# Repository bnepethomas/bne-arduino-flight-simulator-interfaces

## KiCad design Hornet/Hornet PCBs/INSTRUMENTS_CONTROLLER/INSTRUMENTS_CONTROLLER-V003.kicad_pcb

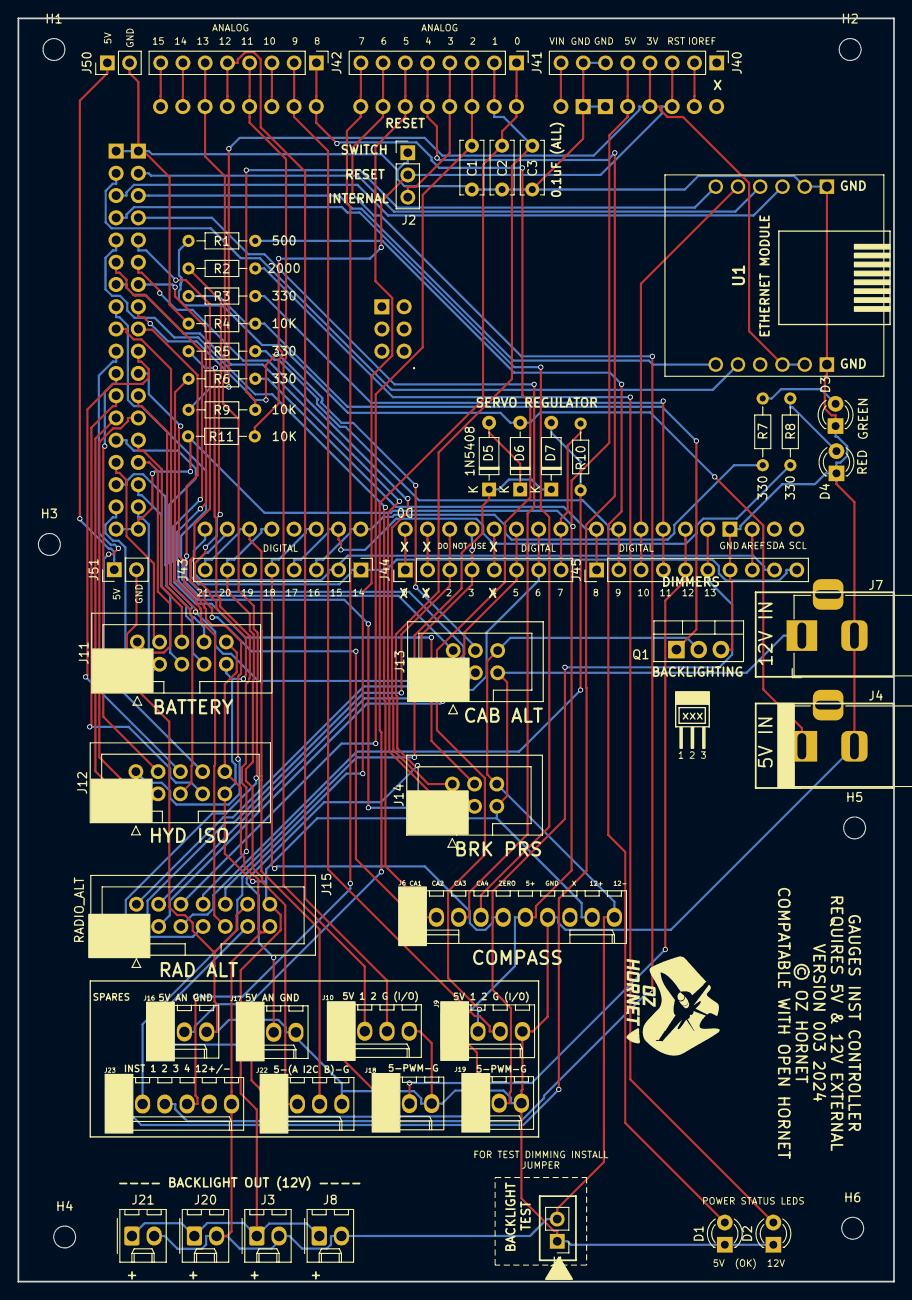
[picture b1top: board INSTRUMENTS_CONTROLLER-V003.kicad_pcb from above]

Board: 2 copper layers, 100.0 x 144.3 mm, 60 parts (0 on the bottom side), 91 nets.

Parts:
A1: Arduino_Mega2560_R3_Shield
C1, C2, C3: 0.1uF; C_Disc_D6.0mm_W2.5mm_P5.00mm
D1, D2: LED; LED_D3.0mm
D3: GREEN; LED_D3.0mm
D4: RED; LED_D3.0mm
D5, D6, D7: 1N5408; D_DO-35_SOD27_P7.62mm_Horizontal
H1, H3, H5: H1; MountingHole_2.5mm
H2, H4, H6: H2; MountingHole_2.5mm
J1: Conn_01x02_Pin; PinHeader_1x02_P2.54mm_Vertical
J2: Conn_01x03_Pin; PinHeader_1x03_P2.54mm_Vertical
J3, J8, J20, J21: 12v-BK/LT; Molex_KK-254_AE-6410-02A_1x02_P2.54mm_Vertical
J4: 5V IN; BarrelJack_Horizontal
J6: COMPASS; Molex_KK-254_AE-6410-10A_1x10_P2.54mm_Vertical
J7: STEPPER IN 12-20VDC; BarrelJack_Horizontal
J9: SPARE I/O-1; Molex_KK-254_AE-6410-04A_1x04_P2.54mm_Vertical
J10: SPARE I/O-2; Molex_KK-254_AE-6410-04A_1x04_P2.54mm_Vertical
J11: BATT-STEPPER; IDC-Header_2x05_P2.54mm_Vertical
J12: HYD-STEPPER; IDC-Header_2x05_P2.54mm_Vertical
J13: CABIN_ALT; IDC-Header_2x03_P2.54mm_Vertical
J14: BRAKE_PRESS; IDC-Header_2x03_P2.54mm_Vertical
J15: RADIO_ALT; IDC-Header_2x07_P2.54mm_Vertical
J16: SPARE A1; Molex_KK-254_AE-6410-03A_1x03_P2.54mm_Vertical
J17: SPARE A2; Molex_KK-254_AE-6410-03A_1x03_P2.54mm_Vertical
J18: SPARE I/O PWM 1; Molex_KK-254_AE-6410-03A_1x03_P2.54mm_Vertical
J19: SPARE I/O PWM 2; Molex_KK-254_AE-6410-03A_1x03_P2.54mm_Vertical
J22: SPARE I2C; Molex_KK-254_AE-6410-04A_1x04_P2.54mm_Vertical
J23: SPARE; Molex_KK-254_AE-6410-06A_1x06_P2.54mm_Vertical
J40, J41, J42, J43, J44: Conn_01x08; PinHeader_1x08_P2.54mm_Vertical
J45: Conn_01x10; PinHeader_1x10_P2.54mm_Vertical
J50, J51: Conn_01x02; PinHeader_1x02_P2.54mm_Vertical
Q1: IRF1405PBF; TO-220-3_Vertical
R1: 500; R_Axial_DIN0204_L3.6mm_D1.6mm_P7.62mm_Horizontal
R2: 2000; R_Axial_DIN0204_L3.6mm_D1.6mm_P7.62mm_Horizontal
R3, R5, R6, R7, R8: 330; R_Axial_DIN0204_L3.6mm_D1.6mm_P7.62mm_Horizontal
R4, R9, R10, R11: 10K; R_Axial_DIN0204_L3.6mm_D1.6mm_P7.62mm_Horizontal
U1: USR-ES1; USRES1

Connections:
+3V3: A1.3V3 (3.3V), J40.4, R9.1, U1.B2 (3V3_1), U1.B3 (3V3_2)
/3.3_V_REG: D5.1 (K), D7.1 (K), J15.10
/+5v_IN: D6.2 (A), J4.1, R1.1
/+12v-IN: J3.1, J6.9, J7.1, J8.1, J11.9, J12.9, J13.5, J14.5, J15.14, J20.1, J21.1, R2.1
/ANALOG_5V: J50.1, J51.1
/AREF: A1.AREF, J45.8
/BACKLIGHT: A1.D11, J45.4, R3.2
/BACKLIGHT_GND: J1.2, J3.2, J6.10, J8.2, J11.10, J12.10, J13.6, J14.6, J15.13, J20.2, J21.2, J23.6, Q1.2 (D)
/BATT-1-1: A1.D22, J11.1
/BATT-1-2: A1.D23, J11.3
/BATT-1-3: A1.D24, J11.5
/BATT-1-4: A1.D25, J11.7
/BATT-2-1: A1.D26, J11.2
/BATT-2-2: A1.D27, J11.4
/BATT-2-3: A1.D28, J11.6
/BATT-2-4: A1.D29, J11.8
/BRK_PRS-COIL-1: A1.D42, J14.1
/BRK_PRS-COIL-2: A1.D43, J14.3
/BRK_PRS-COIL-3: A1.D44, J14.2
/BRK_PRS-COIL-4: A1.D45, J14.4
/CAB_ALT-COIL-1: A1.D38, J13.1
/CAB_ALT-COIL-2: A1.D39, J13.3
/CAB_ALT-COIL-3: A1.D40, J13.4
/CAB_ALT-COIL-4: A1.D41, J13.2
/Compass_Stepper_A: A1.D46, J6.1
/Compass_Stepper_B: A1.D47, J6.2
/Compass_Stepper_C: A1.D48, J6.3
/Compass_Stepper_D: A1.D49, J6.4
/Compass_Zero_Sensor: A1.D16 (D16/TX2), J6.5, J43.5
/D0: A1.D0 (D0/RX0), J44.1
/D1: A1.D1 (D1/TX0), J44.2
/D4: A1.D4, J44.5
/GREEN_LED: A1.D14 (D14/TX3), J43.3, R7.1
/HYD-1-1: A1.D30, J12.1
/HYD-1-2: A1.D31, J12.3
/HYD-1-3: A1.D32, J12.5
/HYD-1-4: A1.D33, J12.7
/HYD-2-1: A1.D34, J12.2
/HYD-2-2: A1.D35, J12.4
/HYD-2-3: A1.D36, J12.6
/HYD-2-4: A1.D37, J12.8
/I2C-A: A1.D18 (D18/TX1), J22.2, J43.7
/I2C-B: A1.D19 (D19/RX1), J22.3, J43.8
/INT_5V: A1.5V1 (5V), A1.5V3 (5V), A1.5V4 (5V), J6.6, J9.1, J10.1, J15.11, J16.1, J17.1, J18.1, J19.1, J22.1, J40.5, R11.1
/OFF_FLAG: A1.D7, J44.8, R10.2
/OFF_FLAG_SIG: D7.2 (A), J15.5, R10.1
/RAD_ALT-1: A1.D2 (D2_INT0), J15.1, J44.3
/RAD_ALT-2: A1.D3 (D3_INT1), J15.2, J44.4
/RAD_ALT-3: A1.D5, J15.3, J44.6
/RAD_ALT-4: A1.D6, J15.4, J44.7
/RAD_ALT-GN_ARDUINO: A1.D9, J45.2, R5.2
/RAD_ALT-GN_LED: J15.8, R5.1
/RAD_ALT-POT: A1.A2, C1.1, J15.6, J41.3
/RAD_ALT-PUSH_BUT: A1.A13, J15.7, J42.6
/RAD_ALT-RD_ARDUINO: A1.D8, J45.1, R6.2
/RAD_ALT-RD_LED: J15.9, R6.1
/RED_LED: A1.D15 (D15/RX3), J43.4, R8.1
/RESET: A1.RST1 (RESET), J2.2, J40.3, R11.2
/RESET_pin: A1.A3, J2.3, J41.4
/SCL: A1.D21 (D21/SCL), J43.1, J45.10
/SDA: A1.D20 (D20/SDA), J43.2, J45.9
/SPARE-COIL-1: A1.A4, J23.1, J41.5
/SPARE-COIL-2: A1.A5, J23.2, J41.6
/SPARE-COIL-3: A1.A6, J23.3, J41.7
/SPARE-COIL-4: A1.A7, J23.4, J41.8
/SPARE_1/O-A0: A1.A0, C2.1, J16.2, J41.1
/SPARE_1/O-A1: A1.A1, C3.1, J17.2, J41.2
/SPARE_I/O-1: A1.A8, J9.2, J42.1
/SPARE_I/O-2: A1.A9, J9.3, J42.2
/SPARE_I/O-4: A1.A11, J10.2, J42.4
/SPARE_I/O-5: A1.A12, J10.3, J42.5
/SPARE_PWM-1: A1.D12, J18.2, J45.5
/SPARE_PWM-2: A1.D13, J19.2, J45.6
/VIN: A1.VIN, J40.8
ES1_RST: A1.D53 (D53_CS), U1.B5 (RST)
GND: A1.GND1 (GND), A1.GND2 (GND), A1.GND3 (GND), A1.GND5 (GND), A1.GND6 (GND), C1.2, C2.2, C3.2, D1.1 (K), D2.1 (K), D3.1 (K), D4.1 (K), J1.1, J2.1, J4.2, J6.7, J7.2, J9.4, J10.4, J15.12, J16.3, J17.3, J18.3, J19.3, J22.4, J40.6, J40.7, J45.7, J50.2, J51.2, Q1.3 (S), R4.1, U1.A1 (GND_1), U1.A2 (GND_2), U1.B1 (GND_3)
MISO: A1.D50 (D50_MISO), U1.B6 (MISO)
MOSI: A1.D51 (D51_MOSI), U1.A3 (MOSI)
unnamed: A1.IORF (IOREF), J40.2
unnamed: D1.2 (A), R1.2
unnamed: D2.2 (A), R2.2
unnamed: D3.2 (A), R7.2
unnamed: D4.2 (A), R8.2
unnamed: D5.2 (A), D6.1 (K)
unnamed: A1.A10, J42.3
unnamed: A1.A14, J42.7
unnamed: A1.A15, J42.8
unnamed: Q1.1 (G), R3.1, R4.2
unnamed: R9.2, U1.A6 (INT)
SCLK: A1.D52 (D52_SCK), U1.A4 (SCLK)
SS: A1.D10, J45.3, U1.A5 (CS)

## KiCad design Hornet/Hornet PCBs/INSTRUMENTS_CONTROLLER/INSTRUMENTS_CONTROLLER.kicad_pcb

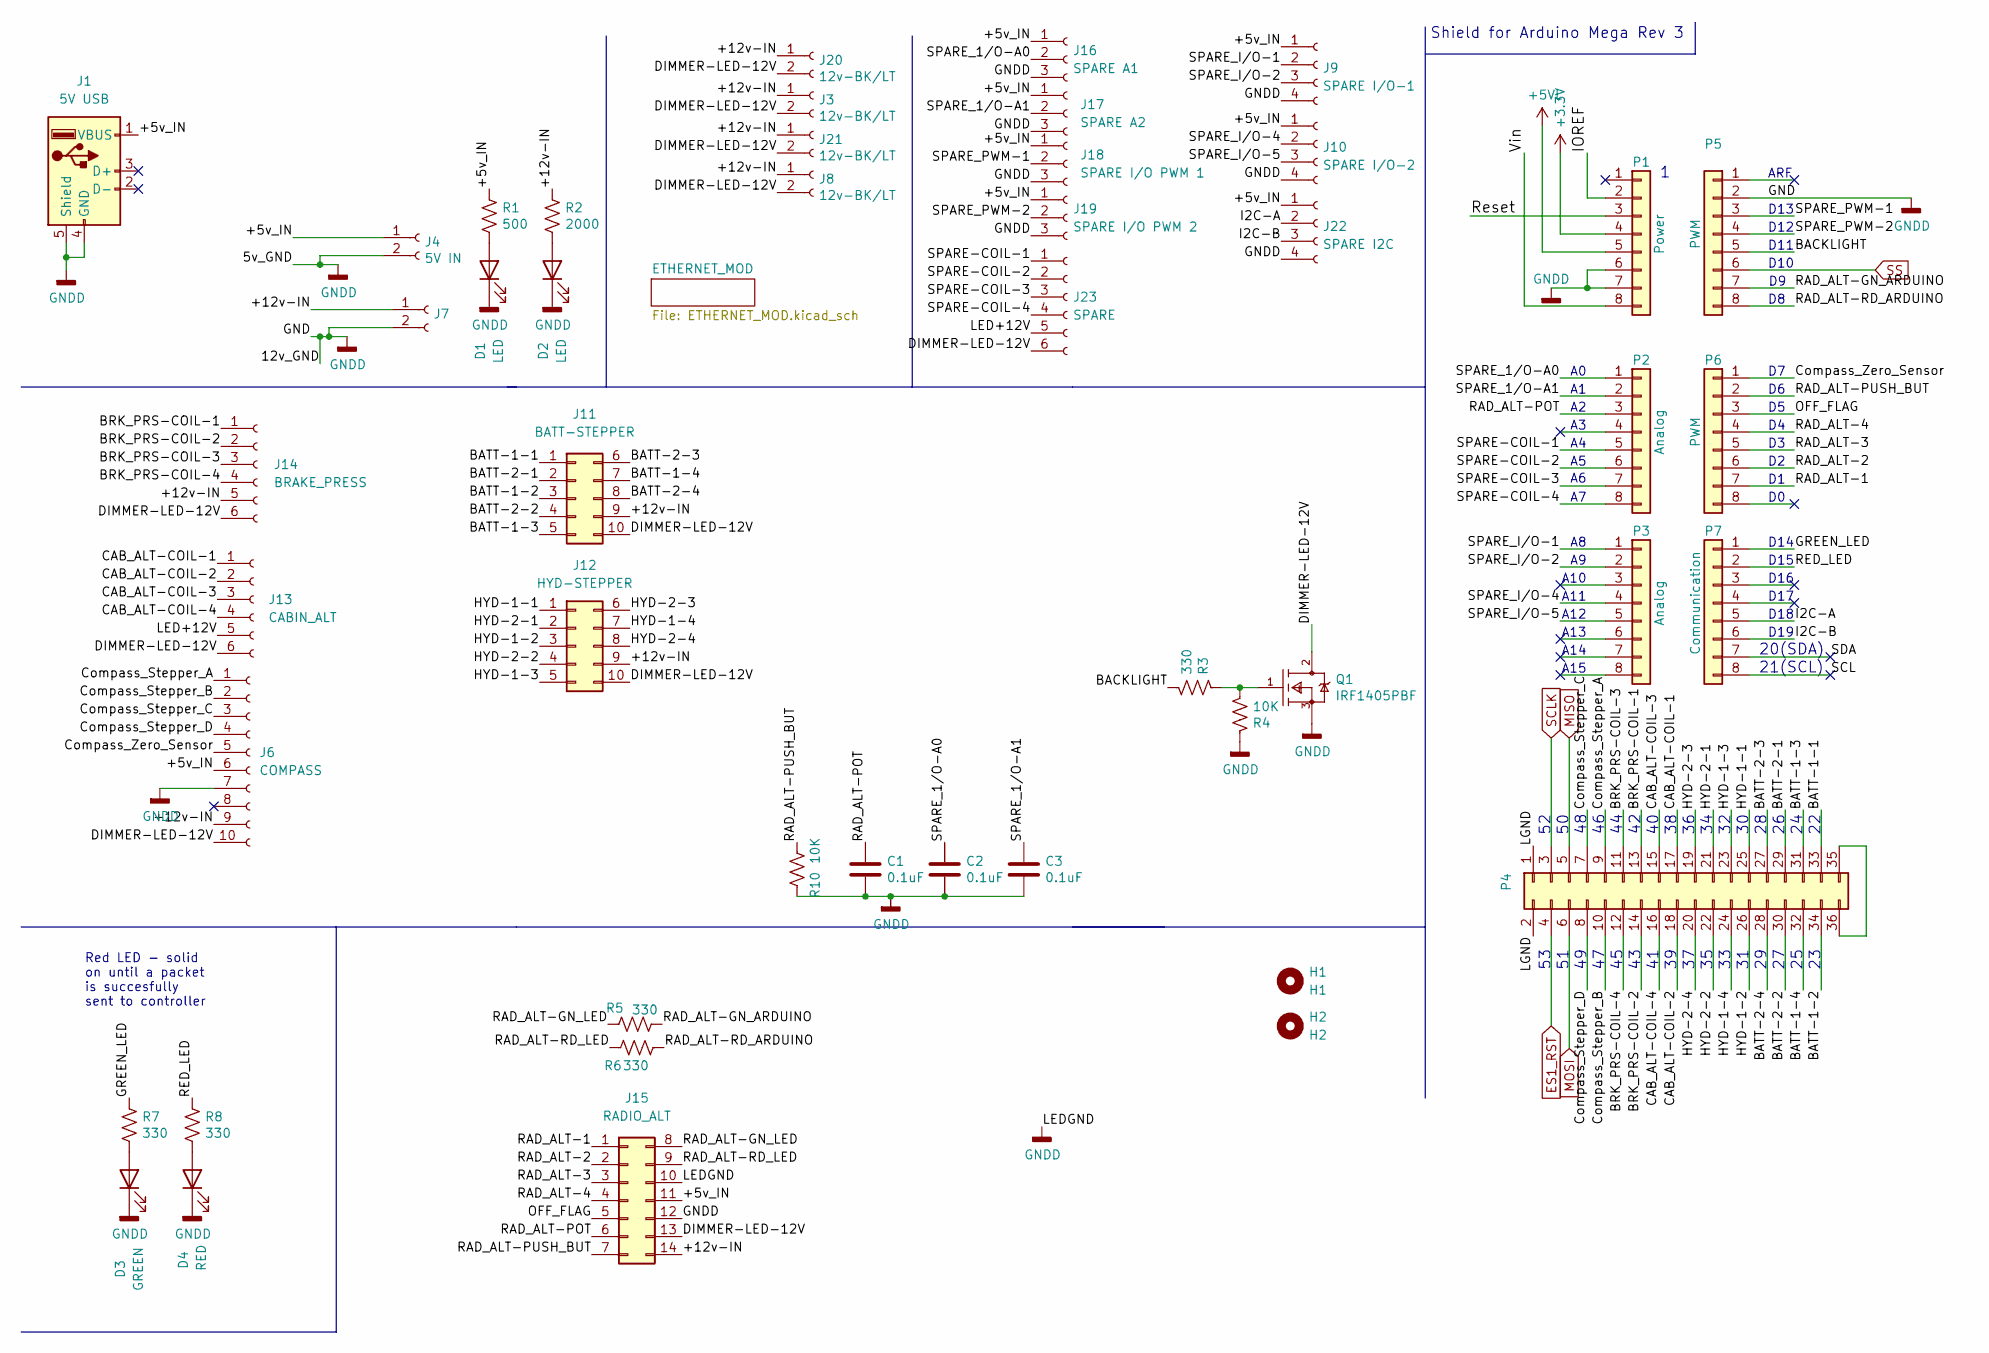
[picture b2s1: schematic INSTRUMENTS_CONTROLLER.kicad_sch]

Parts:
C1, C2, C3: 0.1uF; C_Disc_D6.0mm_W2.5mm_P5.00mm
D1, D2: LED; LED_D3.0mm
D3: GREEN; LED_D3.0mm
D4: RED; LED_D3.0mm
H1: H1; MountingHole_2.5mm
H2: H2; MountingHole_2.5mm
J1: 5V USB; USB_A_Molex_67643_Horizontal
J3, J8, J20, J21: 12v-BK/LT; Molex_KK-254_AE-6410-02A_1x02_P2.54mm_Vertical
J4: 5V IN; BarrelJack_Horizontal
J6: COMPASS; Molex_KK-254_AE-6410-10A_1x10_P2.54mm_Vertical
J7: STEPPER IN 12-20VDC; BarrelJack_Horizontal
J9: SPARE I/O-1; Molex_KK-254_AE-6410-04A_1x04_P2.54mm_Vertical
J10: SPARE I/O-2; Molex_KK-254_AE-6410-04A_1x04_P2.54mm_Vertical
J11: BATT-STEPPER; IDC-Header_2x05_P2.54mm_Vertical
J12: HYD-STEPPER; IDC-Header_2x05_P2.54mm_Vertical
J13: CABIN_ALT; Molex_KK-254_AE-6410-06A_1x06_P2.54mm_Vertical
J14: BRAKE_PRESS; Molex_KK-254_AE-6410-06A_1x06_P2.54mm_Vertical
J15: RADIO_ALT; IDC-Header_2x07_P2.54mm_Vertical
J16: SPARE A1; Molex_KK-254_AE-6410-03A_1x03_P2.54mm_Vertical
J17: SPARE A2; Molex_KK-254_AE-6410-03A_1x03_P2.54mm_Vertical
J18: SPARE I/O PWM 1; Molex_KK-254_AE-6410-03A_1x03_P2.54mm_Vertical
J19: SPARE I/O PWM 2; Molex_KK-254_AE-6410-03A_1x03_P2.54mm_Vertical
J22: SPARE I2C; Molex_KK-254_AE-6410-04A_1x04_P2.54mm_Vertical
J23: SPARE; Molex_KK-254_AE-6410-06A_1x06_P2.54mm_Vertical
P1: Power; Socket_Strip_Arduino_1x08
P2, P3: Analog; Socket_Strip_Arduino_1x08
P4: Digital; Socket_Strip_Arduino_2x18
P5, P6: PWM; Socket_Strip_Arduino_1x08
P7: Communication; Socket_Strip_Arduino_1x08
Q1: IRF1405PBF; TO-220-3_Vertical; mouser part number 942-IRF1405PBF; digikey description MOSFET N-CH 55V 169A TO-220AB
R1: 500; R_Axial_DIN0204_L3.6mm_D1.6mm_P2.54mm_Vertical
R2: 2000; R_Axial_DIN0204_L3.6mm_D1.6mm_P2.54mm_Vertical
R3, R5, R6, R7, R8: 330; R_Axial_DIN0204_L3.6mm_D1.6mm_P2.54mm_Vertical
R4, R10: 10K; R_Axial_DIN0204_L3.6mm_D1.6mm_P2.54mm_Vertical

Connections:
+5VL: P1.5
/+5v_IN: J1.1 (VBUS), J4.1, J6.6, J9.1, J10.1, J15.11, J16.1, J17.1, J18.1, J19.1, J22.1, R1.1
/+12v-IN: J3.1, J6.9, J7.1, J8.1, J11.9, J12.9, J14.5, J15.14, J20.1, J21.1, R2.1
/BACKLIGHT: P5.5, R3.2
/BATT-1-1: J11.1, P4.33
/BATT-1-2: J11.3, P4.34
/BATT-1-3: J11.5, P4.31
/BATT-1-4: J11.7, P4.32
/BATT-2-1: J11.2, P4.29
/BATT-2-2: J11.4, P4.30
/BATT-2-3: J11.6, P4.27
/BATT-2-4: J11.8, P4.28
/BRK_PRS-COIL-1: J14.1, P4.13
/BRK_PRS-COIL-2: J14.2, P4.14
/BRK_PRS-COIL-3: J14.3, P4.11
/BRK_PRS-COIL-4: J14.4, P4.12
/CAB_ALT-COIL-1: J13.1, P4.17
/CAB_ALT-COIL-2: J13.2, P4.18
/CAB_ALT-COIL-3: J13.3, P4.15
/CAB_ALT-COIL-4: J13.4, P4.16
/Compass_Stepper_A: J6.1, P4.9
/Compass_Stepper_B: J6.2, P4.10
/Compass_Stepper_C: J6.3, P4.7
/Compass_Stepper_D: J6.4, P4.8
/Compass_Zero_Sensor: J6.5, P6.1
/DIMMER-LED-12V: J3.2, J6.10, J8.2, J11.10, J12.10, J13.6, J14.6, J15.13, J20.2, J21.2, J23.6, Q1.2 (D)
/GREEN_LED: P7.1, R7.1
/HYD-1-1: J12.1, P4.25
/HYD-1-2: J12.3, P4.26
/HYD-1-3: J12.5, P4.23
/HYD-1-4: J12.7, P4.24
/HYD-2-1: J12.2, P4.21
/HYD-2-2: J12.4, P4.22
/HYD-2-3: J12.6, P4.19
/HYD-2-4: J12.8, P4.20
/I2C-A: J22.2, P7.5
/I2C-B: J22.3, P7.6
/IOREF: P1.2
/LED+12V: J13.5, J23.5
/LGND: P4.1, P4.2
/OFF_FLAG: J15.5, P6.3
/RAD_ALT-1: J15.1, P6.7
/RAD_ALT-2: J15.2, P6.6
/RAD_ALT-3: J15.3, P6.5
/RAD_ALT-4: J15.4, P6.4
/RAD_ALT-GN_ARDUINO: P5.7, R5.2
/RAD_ALT-GN_LED: J15.8, R5.1
/RAD_ALT-POT: C1.1, J15.6, P2.3
/RAD_ALT-PUSH_BUT: J15.7, P6.2, R10.2
/RAD_ALT-RD_ARDUINO: P5.8, R6.2
/RAD_ALT-RD_LED: J15.9, R6.1
/RED_LED: P7.2, R8.1
/Reset: P1.3
/SCL: P7.8
/SDA: P7.7
/SPARE-COIL-1: J23.1, P2.5
/SPARE-COIL-2: J23.2, P2.6
/SPARE-COIL-3: J23.3, P2.7
/SPARE-COIL-4: J23.4, P2.8
/SPARE_1/O-A0: C2.1, J16.2, P2.1
/SPARE_1/O-A1: C3.1, J17.2, P2.2
/SPARE_I/O-1: J9.2, P3.1
/SPARE_I/O-2: J9.3, P3.2
/SPARE_I/O-4: J10.2, P3.4
/SPARE_I/O-5: J10.3, P3.5
/SPARE_PWM-1: J18.2, P5.3
/SPARE_PWM-2: J19.2, P5.4
/Vin: P1.8
ES1_RST: P4.4; also elsewhere on the board
MISO: P4.5; also elsewhere on the board
MOSI: P4.6; also elsewhere on the board
unnamed: D1.2 (A), R1.2
unnamed: D2.2 (A), R2.2
unnamed: D3.2 (A), R7.2
unnamed: D4.2 (A), R8.2
unnamed: P4.35, P4.36
unnamed: Q1.1 (G), R3.1, R4.2
SCLK: P4.3; also elsewhere on the board
SS: P5.6; also elsewhere on the board

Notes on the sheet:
A14
ARF
Shield for Arduino Mega Rev 3
D10
D13
Red LED - solid on until a packet is succesfully sent to controller
A13
A12
D14
A15
D15
D12
A11
D17
D11
20(SDA)
21(SCL)
D19
D16
A10
D18

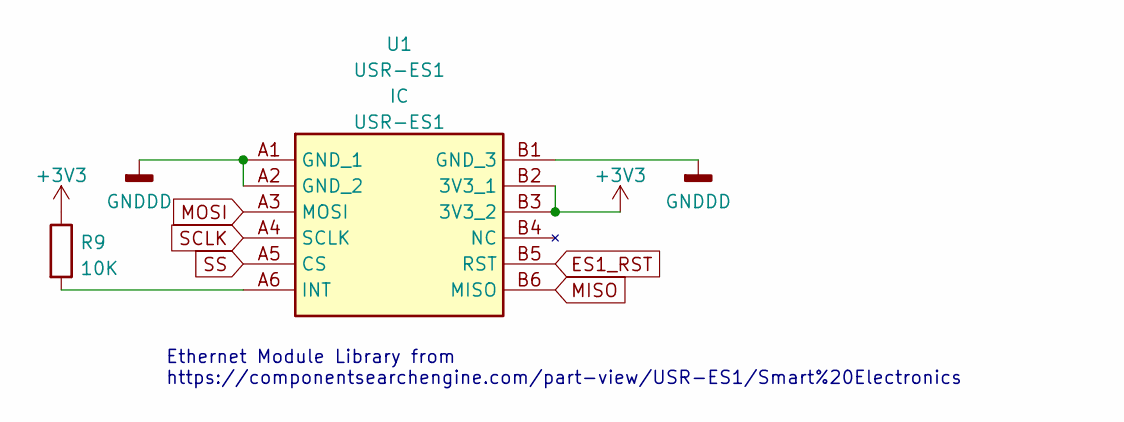
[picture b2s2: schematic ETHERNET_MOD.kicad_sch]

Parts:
R9: 10K; R_Axial_DIN0204_L3.6mm_D1.6mm_P2.54mm_Vertical
U1: USR-ES1; USRES1; Manufacturer_Part_Number USR-ES1

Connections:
ES1_RST: U1.B5 (RST); also elsewhere on the board
MISO: U1.B6 (MISO); also elsewhere on the board
MOSI: U1.A3 (MOSI); also elsewhere on the board
unnamed: R9.2, U1.A6 (INT)
SCLK: U1.A4 (SCLK); also elsewhere on the board
SS: U1.A5 (CS); also elsewhere on the board

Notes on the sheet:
Ethernet Module Library from https://componentsearchengine.com/part-view/USR-ES1/Smart%20Electronics

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
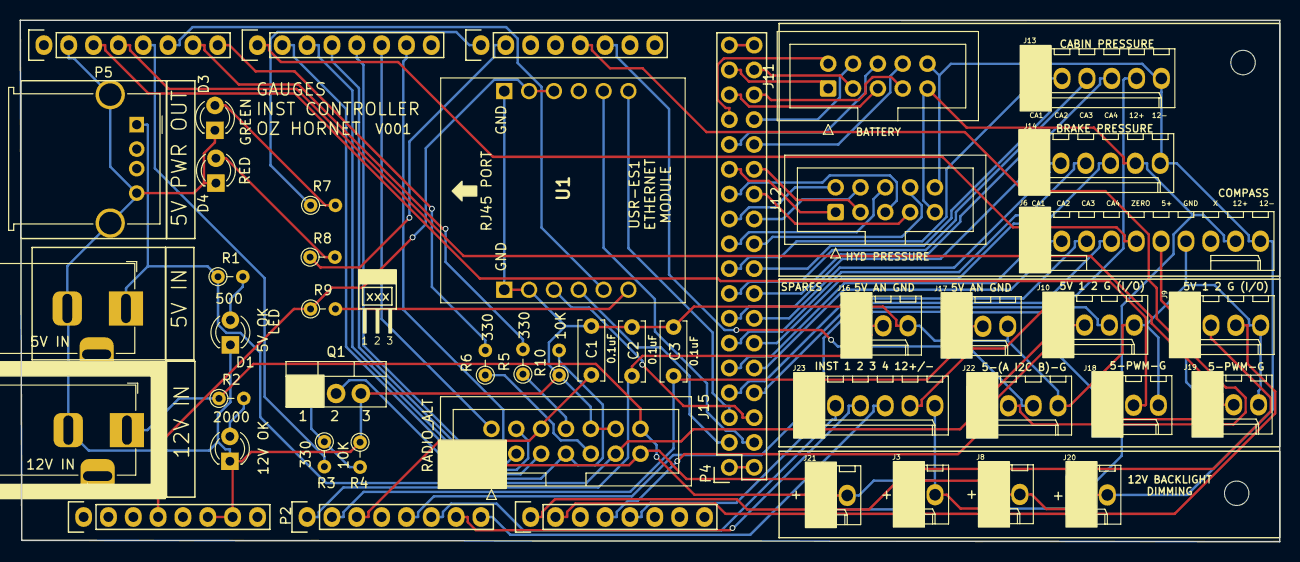
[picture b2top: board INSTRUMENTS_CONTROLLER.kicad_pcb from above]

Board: 2 copper layers, 128.8 x 53.3 mm, 49 parts (0 on the bottom side), 76 nets.

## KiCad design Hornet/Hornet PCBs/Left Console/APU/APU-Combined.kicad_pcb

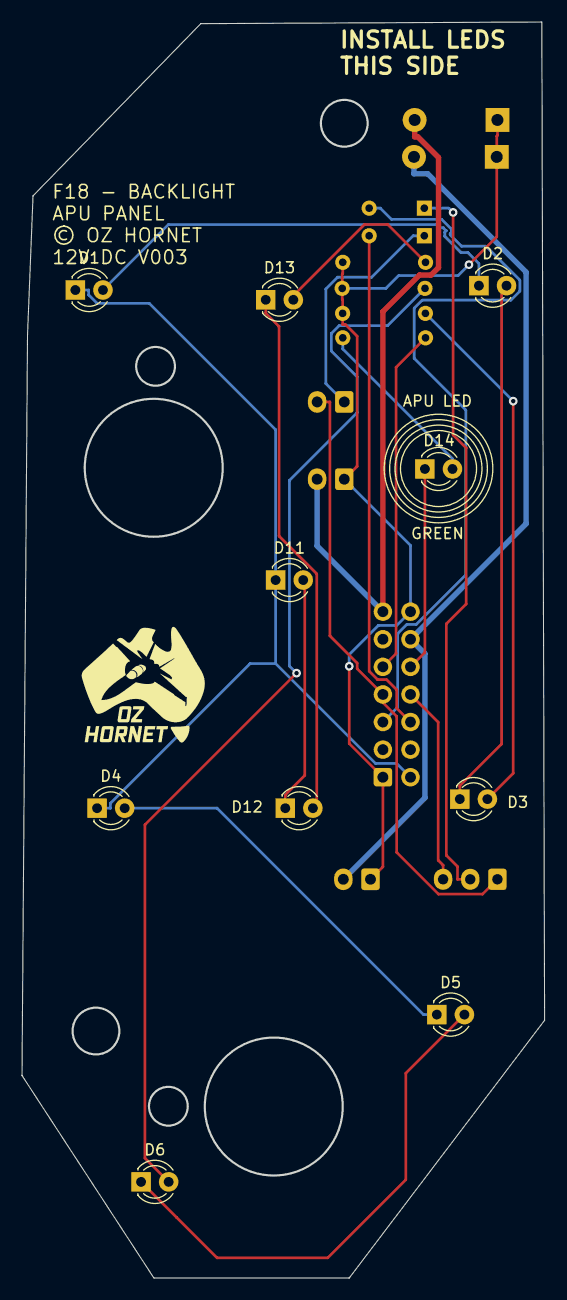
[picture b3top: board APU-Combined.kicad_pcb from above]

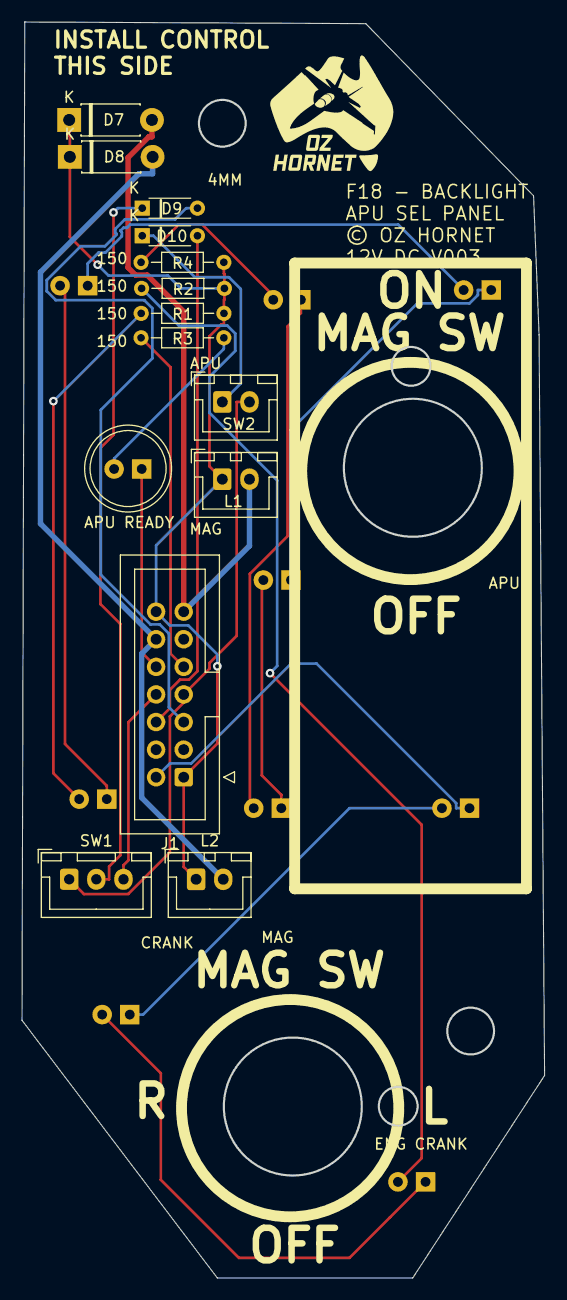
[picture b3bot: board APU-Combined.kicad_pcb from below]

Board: 2 copper layers, 48.1 x 115.6 mm, 23 parts (13 on the bottom side), 22 nets.

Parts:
D1, D2, D3, D4, D5, D6, D11, D12, D13, D14: LED; LED_D3.0mm_FlatTop
D7, D8: D; D_DO-41_SOD81_P7.62mm_Horizontal
D9, D10: D; D_A-405_P7.62mm_Horizontal-SIGNAL
J1: Conn_02x07_Top_Bottom; IDC-Header_2x07_P2.54mm_Vertical
L1: APU Coil; JST_XH_B2B-XH-A_1x02_P2.50mm_Vertical
L2: Crank Coil; JST_XH_B2B-XH-A_1x02_P2.50mm_Vertical
R1, R2, R3, R4: R; R_Axial_DIN0204_L3.6mm_D1.6mm_P7.62mm_Horizontal
SW1: ENG CRANK; JST_XH_B3B-XH-A_1x03_P2.50mm_Vertical
SW2: APU; JST_XH_B2B-XH-A_1x02_P2.50mm_Vertical

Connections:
/APU_LED_RES: J1.9, R3.1
/APU_MAG_SW: D7.2 (A), J1.13, L1.2
/BACKLIGHT_GND: D1.1 (K), D4.1 (K), D11.1 (K), J1.2
/CRANK_MAG_SW: D8.2 (A), J1.12, L2.2
/Col1: D9.2 (A), J1.5
/Col2: D10.2 (A), J1.6
/EXT+12V: D7.1 (K), D8.1 (K), J1.1, J1.14, L1.1, L2.1, R1.2, R2.2, R4.2
/GND: D14.1 (K), J1.10
/Row1: J1.7, SW1.1, SW2.2 (B)
/Row2: J1.8, SW1.3
unnamed: D1.2 (A), D2.1 (K)
unnamed: D2.2 (A), D3.1 (K)
unnamed: D3.2 (A), R1.1
unnamed: D4.2 (A), D5.1 (K)
unnamed: D5.2 (A), D6.1 (K)
unnamed: D6.2 (A), R2.1
unnamed: D9.1 (K), SW1.2
unnamed: D10.1 (K), SW2.1 (A)
unnamed: D11.2 (A), D12.1 (K)
unnamed: D12.2 (A), D13.1 (K)
unnamed: D13.2 (A), R4.1
unnamed: D14.2 (A), R3.2

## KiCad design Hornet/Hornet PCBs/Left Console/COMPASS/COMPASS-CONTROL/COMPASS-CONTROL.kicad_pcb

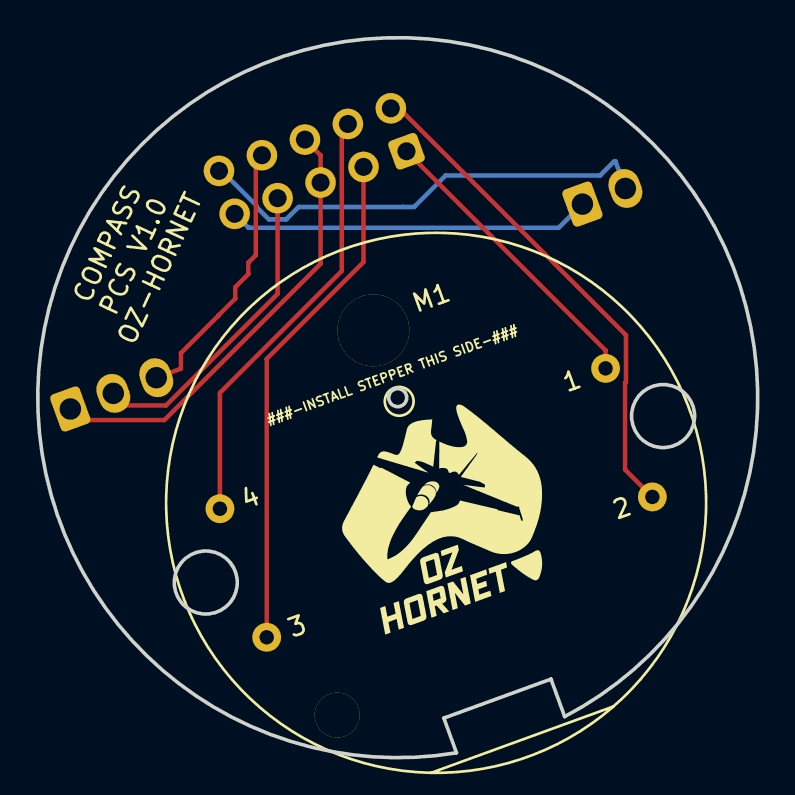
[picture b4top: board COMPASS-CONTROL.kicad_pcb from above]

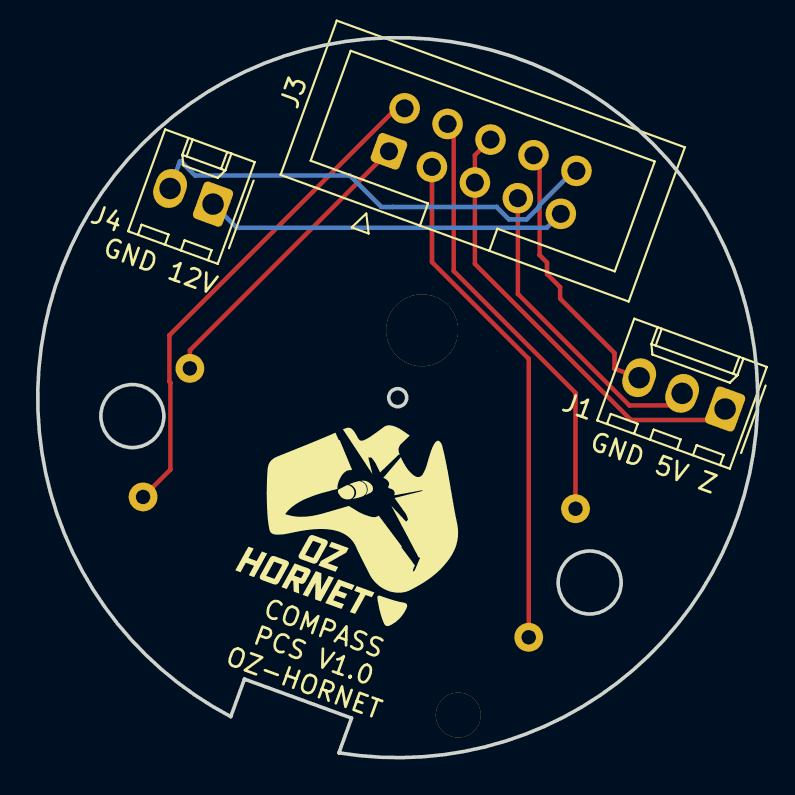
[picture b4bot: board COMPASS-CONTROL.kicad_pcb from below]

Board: 2 copper layers, 40.0 x 40.0 mm, 4 parts (3 on the bottom side), 9 nets.

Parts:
J1: Conn_01x03_Socket; Molex_KK-254_AE-6410-03A_1x03_P2.54mm_Vertical
J3: Conn_02x05_Counter_Clockwise; IDC-Header_2x05_P2.54mm_Vertical
J4: Conn_01x02_Socket; Molex_KK-254_AE-6410-02A_1x02_P2.54mm_Vertical
M1: X27 168; X27-168

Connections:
/5V: J1.2, J3.7
/+12v-IN: J3.9, J4.1
/BACKLIGHT_GND: J3.10, J4.2
/Compass_Zero_Sensor: J1.1, J3.5, J3.6
/GND: J1.3, J3.8
/STEPPER-1-1: J3.1, M1.1
/STEPPER-1-2: J3.2, M1.2 (-)
/STEPPER-1-3: J3.3, M1.3
/STEPPER-1-4: J3.4, M1.4

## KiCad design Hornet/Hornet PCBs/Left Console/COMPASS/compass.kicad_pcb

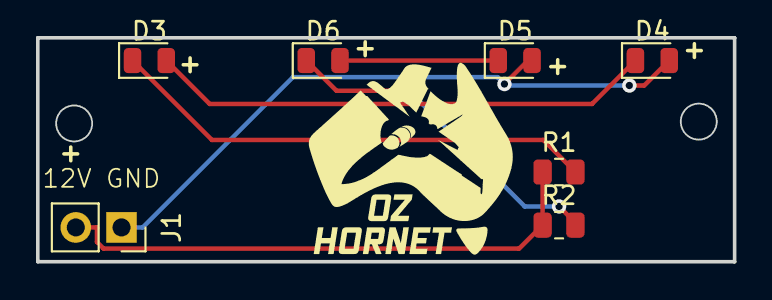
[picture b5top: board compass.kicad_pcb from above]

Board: 2 copper layers, 38.7 x 12.4 mm, 7 parts (0 on the bottom side), 6 nets.

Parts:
D3, D4, D5, D6: LED; LED_0805_2012Metric
J1: Conn_01x02; PinSocket_1x02_P2.54mm_Vertical
R1, R2: R; R_0805_2012Metric

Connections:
/LED+12V: D4.2 (A), D5.2 (A), J1.1
/LED-12V: J1.2, R1.1, R2.1
unnamed: D3.2 (A), D4.1 (K)
unnamed: D3.1 (K), R1.2
unnamed: D5.1 (K), D6.2 (A)
unnamed: D6.1 (K), R2.2

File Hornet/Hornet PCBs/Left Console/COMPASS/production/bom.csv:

Designator,Footprint,Quantity,Value,LCSC Part #
"D3, D4, D5, D6",0805,4,LED,
J1,PinSocket_1x02_P2.54mm_Vertical,1,Conn_01x02,
"R1, R2",0805,2,R,

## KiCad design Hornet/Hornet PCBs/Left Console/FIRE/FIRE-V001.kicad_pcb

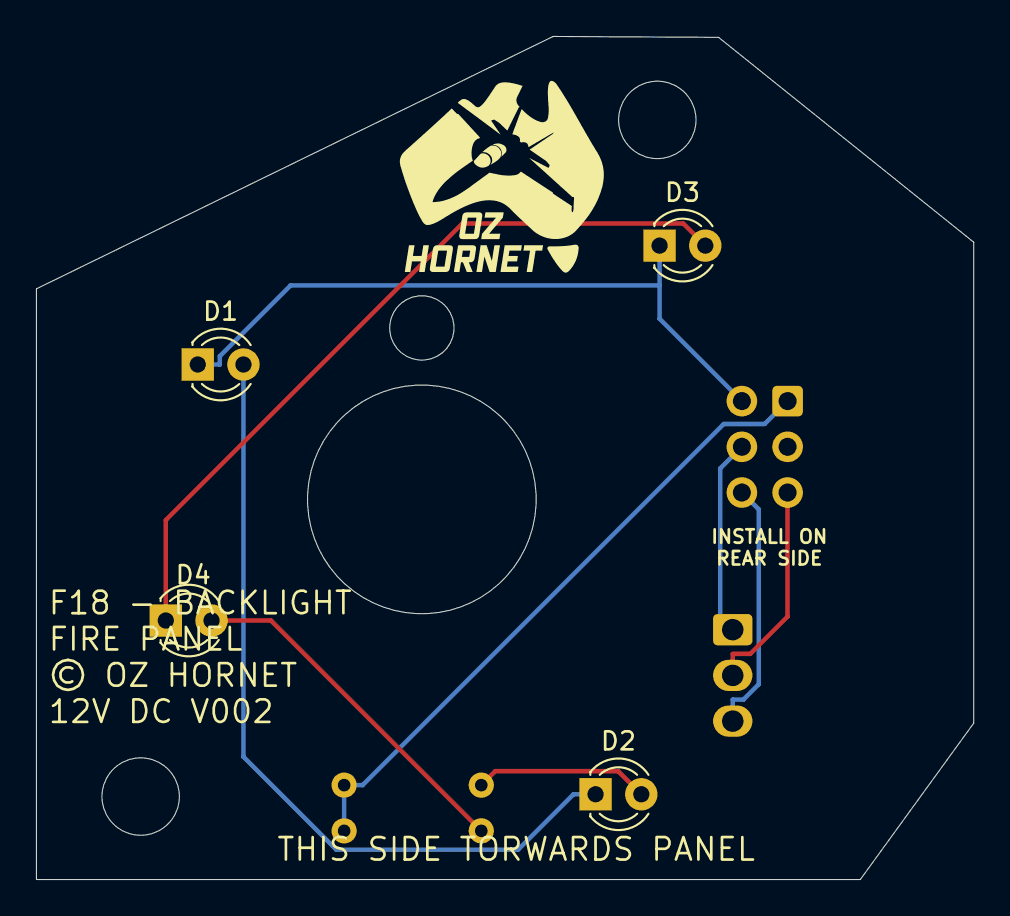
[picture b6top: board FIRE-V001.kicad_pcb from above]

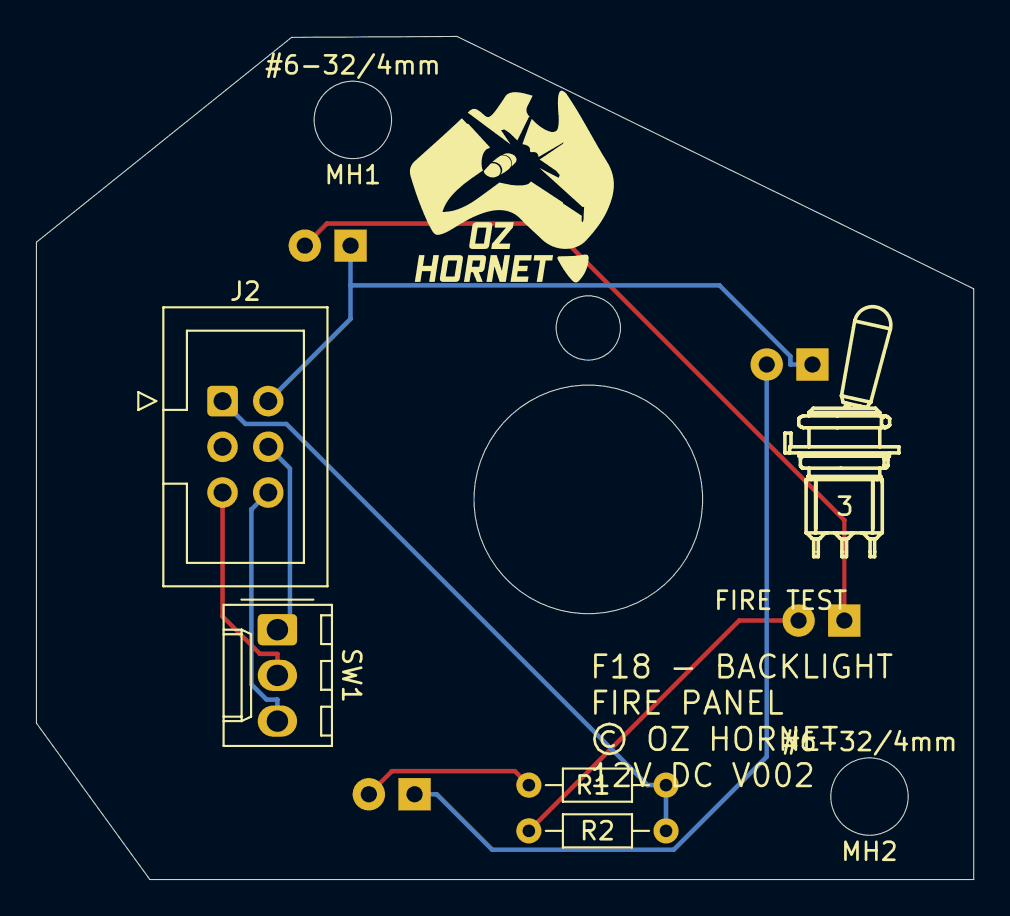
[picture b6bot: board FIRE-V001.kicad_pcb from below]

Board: 2 copper layers, 52.1 x 46.8 mm, 12 parts (7 on the bottom side), 9 nets.

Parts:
D1, D2, D3, D4: LED; LED_D3.0mm_FlatTop
J2: CABIN_ALT; IDC-Header_2x03_P2.54mm_Vertical
LOGO3: LOGO; 100SP3_Toggle_Silkscreen
MH1, MH2: 6x32 / 4mm; MountingHole_6-32_PHS
MH3: Switch_100SPx; 100SPX_Toggle_13mm_x_18mm
R1, R2: R; R_Axial_DIN0204_L3.6mm_D1.6mm_P7.62mm_Horizontal
SW1: FIRE; Molex_KK-254_AE-6410-03A_1x03_P2.54mm_Vertical

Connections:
/BACKLIGHT_12V: J2.1, R1.2, R2.2
/BACKLIGHT_GND: D1.1 (K), D3.1 (K), J2.2
/COM: J2.5, SW1.2 (3)
/TEST_A: J2.4, SW1.1
/TEST_B: J2.6, SW1.3 (4)
unnamed: D1.2 (A), D2.1 (K)
unnamed: D2.2 (A), R1.1
unnamed: D3.2 (A), D4.1 (K)
unnamed: D4.2 (A), R2.1

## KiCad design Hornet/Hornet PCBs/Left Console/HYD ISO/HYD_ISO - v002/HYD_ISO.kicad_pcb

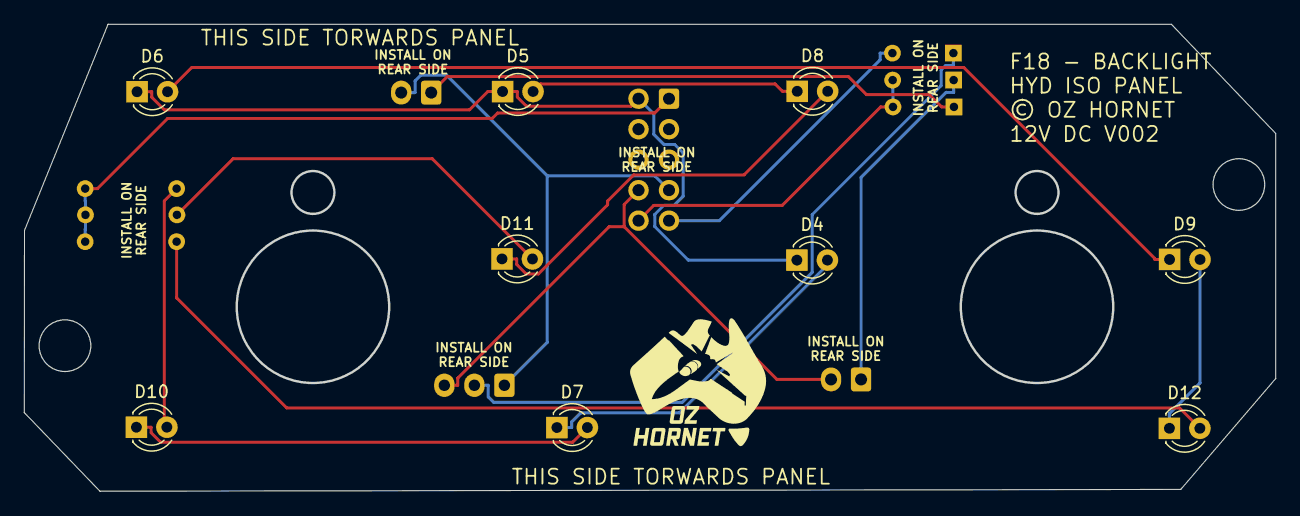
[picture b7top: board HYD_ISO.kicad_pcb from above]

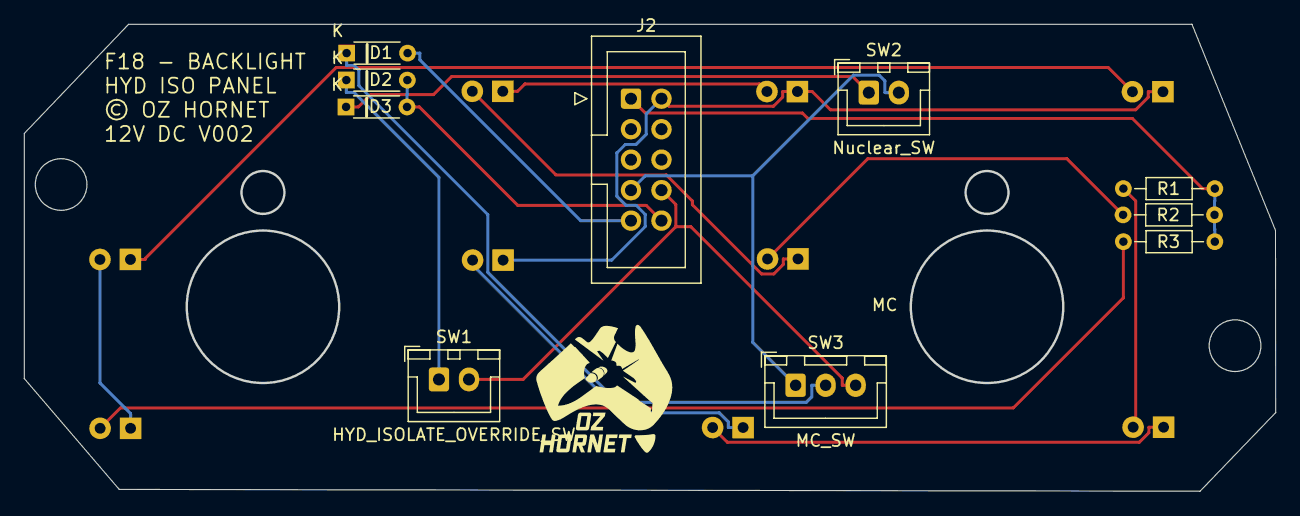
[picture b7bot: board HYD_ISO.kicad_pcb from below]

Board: 2 copper layers, 104.3 x 38.9 mm, 19 parts (10 on the bottom side), 18 nets.

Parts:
D1, D2, D3: D; D_A-405_P7.62mm_Horizontal-SIGNAL
D4, D5, D6, D7, D8, D9, D10, D11, D12: LED; LED_D3.0mm_FlatTop
J2: Conn_02x05_Top_Bottom; IDC-Header_2x05_P2.54mm_Vertical
R1, R2, R3: R; R_Axial_DIN0204_L3.6mm_D1.6mm_P7.62mm_Horizontal
SW1: HYD_ISOLATE_OVERRIDE_SW; JST_XH_B2B-XH-A_1x02_P2.50mm_Vertical
SW2: Nuclear_SW; JST_XH_B2B-XH-A_1x02_P2.50mm_Vertical
SW3: MC_SW; JST_XH_B3B-XH-A_1x03_P2.50mm_Vertical

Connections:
/BACKLIGHT_12V: J2.1, R1.2, R2.2, R3.2
/BACKLIGHT_GND: D4.1 (K), D5.1 (K), D6.1 (K), J2.2
/Col1: D1.2 (A), J2.9
/Col2: D2.2 (A), D3.2 (A), J2.10
/Row1: J2.7, SW2.2 (B), SW3.1
/Row2: J2.8, SW1.2 (B), SW3.3 (4)
unnamed: D1.1 (K), SW3.2 (3)
unnamed: D2.1 (K), SW1.1 (A)
unnamed: D3.1 (K), SW2.1 (A)
unnamed: D4.2 (A), D7.1 (K)
unnamed: D5.2 (A), D8.1 (K)
unnamed: D6.2 (A), D9.1 (K)
unnamed: D10.2 (A), R1.1
unnamed: D7.2 (A), D10.1 (K)
unnamed: D11.2 (A), R2.1
unnamed: D8.2 (A), D11.1 (K)
unnamed: D12.2 (A), R3.1
unnamed: D9.2 (A), D12.1 (K)

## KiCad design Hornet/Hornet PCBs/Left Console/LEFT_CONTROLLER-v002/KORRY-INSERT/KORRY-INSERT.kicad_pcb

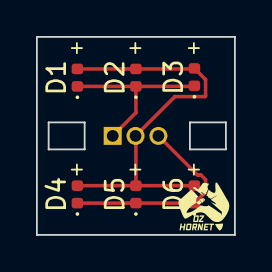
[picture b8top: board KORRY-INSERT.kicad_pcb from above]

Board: 2 copper layers, 11.0 x 11.0 mm, 7 parts (1 on the bottom side), 3 nets.

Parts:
D1, D2, D3, D4, D5, D6: LED; LED_0402_1005Metric
J1: Conn_01x03_Pin; PinHeader_1x03_P1.27mm_Vertical

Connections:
/COL_X: D1.2 (A), D2.2 (A), D3.2 (A), D4.2 (A), D5.2 (A), D6.2 (A), J1.2
/ROW_Y: D1.1 (K), D2.1 (K), D3.1 (K), J1.1
/ROW_Z: D4.1 (K), D5.1 (K), D6.1 (K), J1.3

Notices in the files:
Hornet/Hornet PCBs/INSTRUMENTS_CONTROLLER/INSTRUMENTS_CONTROLLER-V003.kicad_pcb:
© OZ HORNET
Hornet/Hornet PCBs/Left Console/HYD ISO/HYD_ISO - v002/HYD_ISO.kicad_pcb:
License:  CC BY-NC-SA
